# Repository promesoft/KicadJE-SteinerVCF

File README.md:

# Johansen Engineering Steiner VCF RevB

# Status - VCF working
## Initial 
| Stage  | Detail | Status |
| ------------- | ------------- | ------------- |
| create material  | sch/pcb | OK  |
| | gerber | OK |
| production  |   | OK |
|  | produced | OK |
|  | delivered | Delivered |
## Preliminary validation
| Test  | Detail | Status |
| ------------- | ------------- | ------------- |
| Initial Inspection | VCO | OK - bottom looks empty w/o gnd fill |
| Initial Inspection | VCF | OK - bottom looks empty w/o gnd fill |
| | | Very difficult to mount as footprints are getting over soldering points in many places|
| | | BP in the bottom |
| | | HP in the middle |
| | | LP on top |
| Initial Inspection | VCF SMD | OK - bottom looks empty w/o gnd fill |
| Initial Technical Test | VCO | SINE has PCB error - and Sine pot has +12V to chassis |
| Initial Technical Test | VCF | One pot gets -12v on chassis |
| Initial Technical Test | VCF SMD |  |
| Initial Product Test | VCO | Nice -  |
| Initial Product Test | VCF |  |
| | | CV1 and CV2 works fine |
| | | Q is doing something |
| | | Uncertain if the freq pot is right |
| Initial Product Test | VCF SMD|  |
## Secondary validation
| Test  | Detail | Status |
| ------------- | ------------- |------------- |
| Product Test |  | |
| Product Test |  |  |
| Quality | | |
| Quality | | |
| Long Term Product Test |  |  |
| Power Draw | VCO | +12 4mA -12
| Power Draw | VCF | +12 8mA -12
| Power Draw | VCF SMD | +12 ?mA -12

## Errata
### Errata - VCO
* Due to footprint one of the pots gets -12v on chassis

* Sine signal is shorted to GND

* Glide pot is reversed

### Errata - VCF
* Due to footprint one of the pots gets -12v on chassis

* R127 - DNP (Do not populate)

* R119 swap with 220nF-1uF to ac couple input stage

* R126 swap with 1uF to ac couple input stage

### Errata - VCF SMD

## Issues and Notes
### VCF
Very difficult to mount as footprints are getting over soldering points in many places
### VCO
 * Remove output pots
 * Collect jacks in the bottom
 * Fix errors (glide,  POT, PCB errors, footprint tightened)
 * Consider removing sine shaper
# Pictures

# Schematic

# Layout

# Inspiration

-----------------------

# Johansen Engineering Steiner VCF

# Purpose
Test some of the original designs for inspiration and reference.

# Status - Preliminary tests
## Initial 
| Stage  | Detail | Status |
| ------------- | ------------- | ------------- |
| create material  | sch/pcb | produced Rev A  |
| | gerber | produced and uploaded RevA |
| production  | ordered  | OK |
|  | produced | OK |
|  | delivered | OK |
## Preliminary validation
| Test  | Detail | Status |
| ------------- | ------------- | ------------- |
| Initial Inspection | THT VCF - Visual - Component Mounting | NOT OK |
| Initial Inspection | SMD VCF - Visual - Component Mounting | NOT OK |
| Initial Inspection | VCO  - Visual - Component Mounting | OK |
| Initial Technical Test | THT VCF - Base operation | NOT OK |
| | Knobs | Freq working for LP - Q for HP/BP - CV trim - not ok|
| Initial Technical Test | SMD VCF | NOT TESTED |
| Initial Technical Test | VCO  - Sine - Triangle - Square | OK |
| | Trimmers | OK |
| | Knobs | OK |
| Initial Product Test | VCO CV from LFO | OK |
| | VCO Vactrol CV from LFO | no real effect with CV coupling |

## Secondary validation
| Test  | Detail | Status |
| ------------- | ------------- |------------- |
| Product Test | VCF | |
| Product Test | VCO | Works nicely - frequency is a bit high |
| Quality | VCF | |
| Quality | VCO | |
| Long Term Product Test | VCO | OpAmp gets hot - esp if no output is conn to the square |
| Power Draw | VCO | 50-120mA depending on output...

## Errata
### Errata - THT VCF
 * C111 reverse polarity
 * R102 should go from +10v to connection between R103 and R106 - and +10v sould not go to Q102 base - Critical
### Errata - SMD VCF
 * R should go from +10v to connection between R and R - and +10v sould not go to Q base - Critical
### Errata - VCO
 * 470K values not correct for all resistors
 * 0R values not correct - fixed in RevB
 * Outputs should not be shorted to GND when not connected
 
## Issues and Notes
### VCF THT/SMD
 * The filter needs adjustments and the feedback is not stable. a 56k from CV to base of Q102 helps a bit.
 * Input circuit for CV needs rework
 * Input series resistor and capacitor could be a good addon for the filter inputs
 * Frequency adjust seems to work for LP only
 * Q adjust is minor and seems to work on HP and a bit on BP

### VCO
 * Tweak values for better frequency range
 * Op Amp can get hot
 * Draws more power if nothing is inserted into the Square output?

# Physical Construction

# Features

## SMD VCF Schematic

## VCO Schematic

# Inspirational sources:
## Steiner VCF 1974 THT

## Steiner VCF 1974 SMD
Same schematic - different components - half the size

## VCO ICL 8083
Based on a Thomas Henry schematic

# Details

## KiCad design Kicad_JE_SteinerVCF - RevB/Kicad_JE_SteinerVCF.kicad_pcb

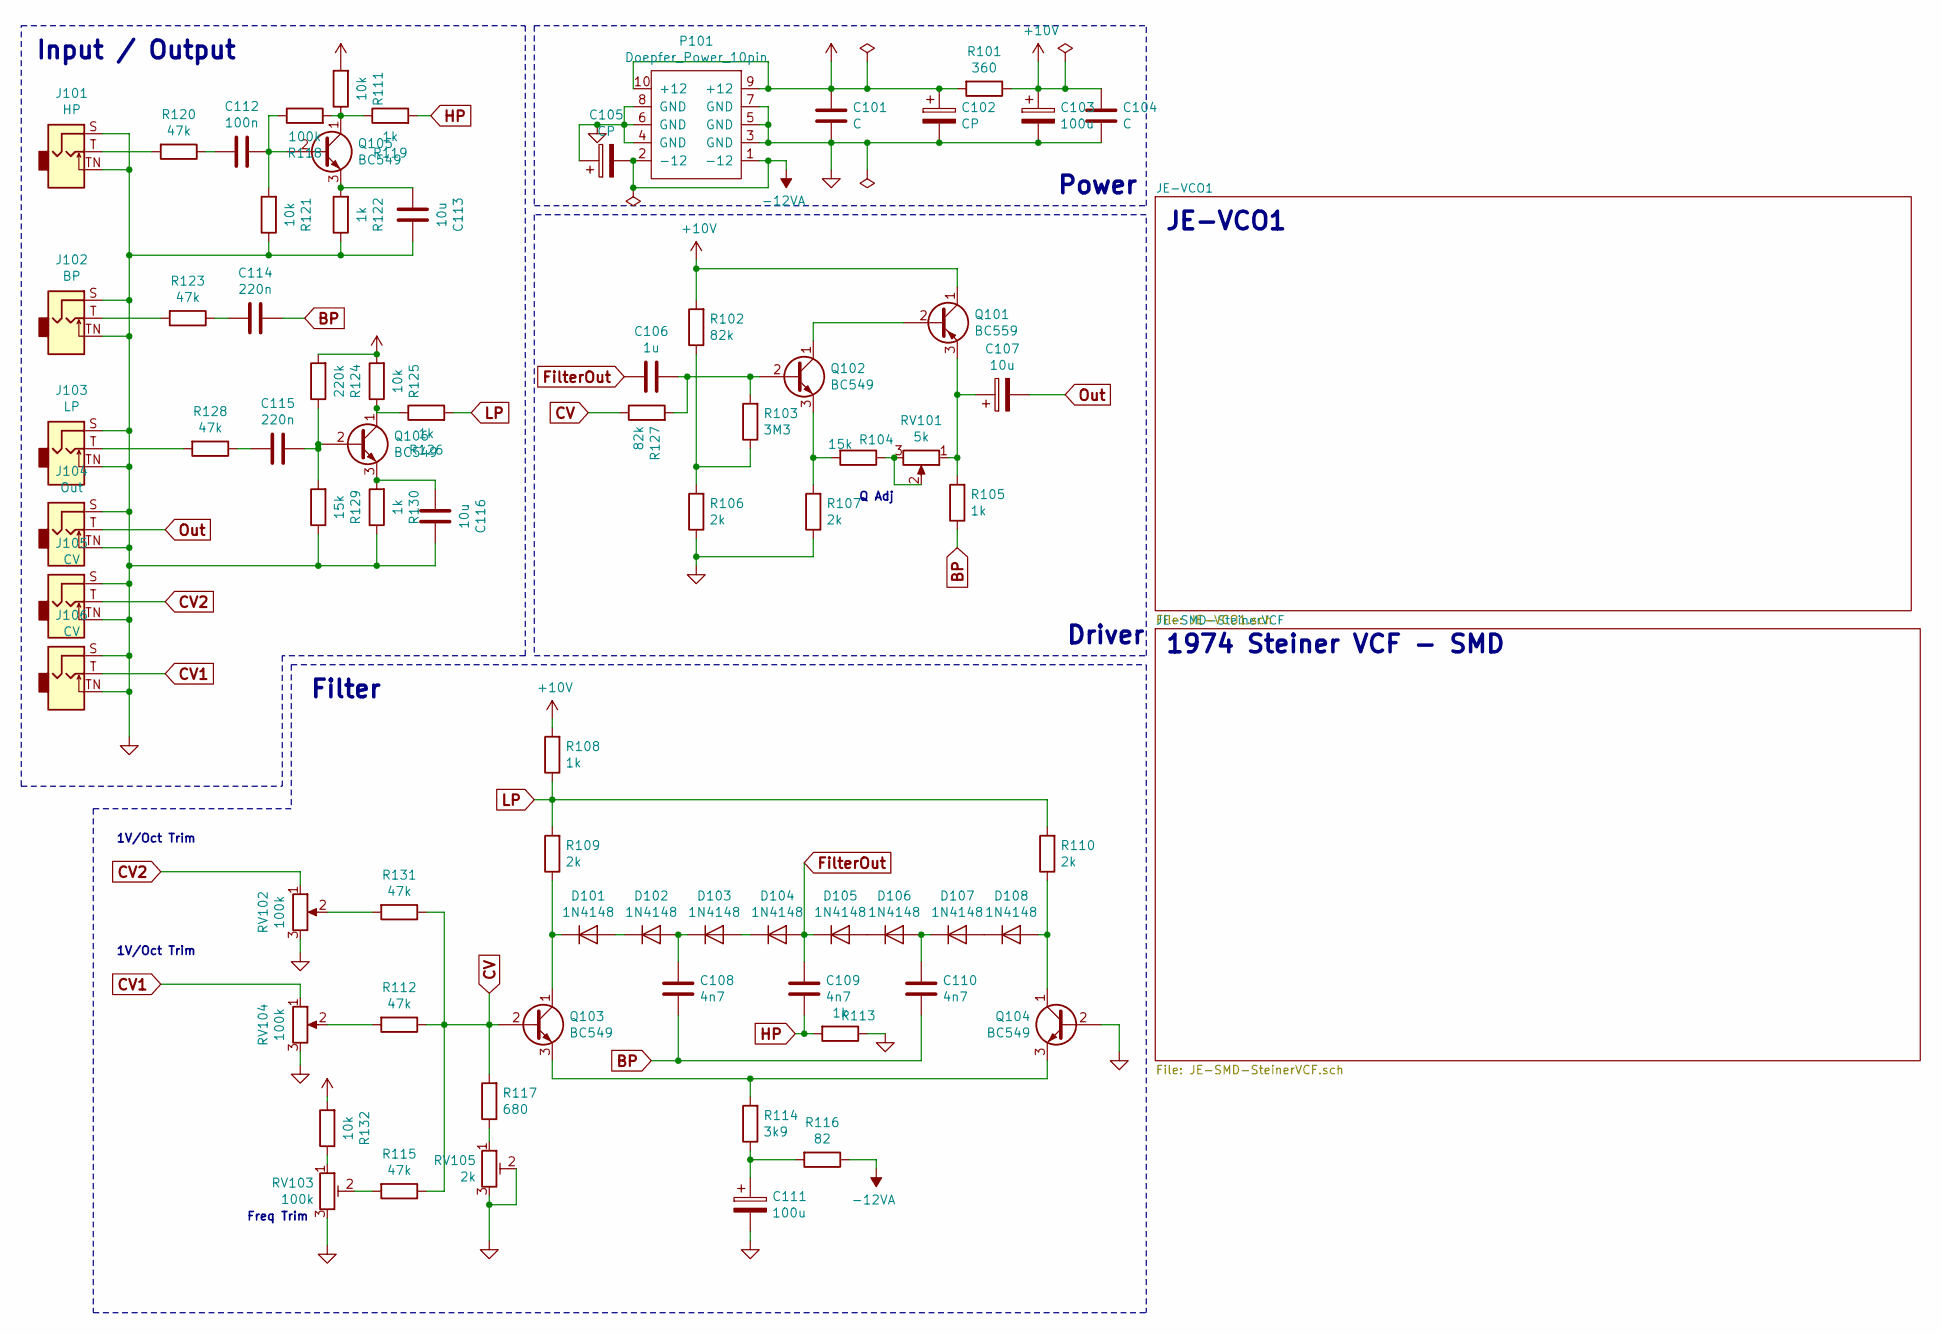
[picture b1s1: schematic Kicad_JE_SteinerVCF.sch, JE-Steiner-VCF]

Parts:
C101, C104: C; C_Rect_L7.0mm_W2.0mm_P5.00mm
C102, C105: CP; CP_Radial_D10.0mm_P5.00mm
C103, C111: 100u; CP_Radial_D10.0mm_P5.00mm
C106: 1u; C_Rect_L7.0mm_W2.0mm_P5.00mm
C107: 10u; CP_Radial_D10.0mm_P3.80mm
C108, C109, C110: 4n7; C_Rect_L7.0mm_W2.0mm_P5.00mm
C112: 100n; C_Rect_L7.0mm_W2.0mm_P5.00mm
C113, C116: 10u; C_Rect_L7.0mm_W2.0mm_P5.00mm
C114, C115: 220n; C_Rect_L7.0mm_W2.0mm_P5.00mm
D101, D102, D103, D104, D105, D106, D107, D108: 1N4148; D_DO-35_SOD27_P7.62mm_Horizontal
J101: HP; PJ301SM
J102: BP; PJ301SM
J103: LP; PJ301SM
J104: Out; PJ301SM
J105, J106: CV; PJ301SM
P101: Doepfer_Power_10pin; IDC-Header_2x05_Pitch2.54mm_Straight
Q101: BC559; TO-92_Inline
Q102, Q103, Q104, Q105, Q106: BC549; TO-92_Inline
R101: 360; R_Axial_DIN0309_L9.0mm_D3.2mm_P12.70mm_Horizontal
R102, R127: 82k; R_Axial_DIN0309_L9.0mm_D3.2mm_P12.70mm_Horizontal
R103: 3M3; R_Axial_DIN0309_L9.0mm_D3.2mm_P12.70mm_Horizontal
R104, R129: 15k; R_Axial_DIN0309_L9.0mm_D3.2mm_P12.70mm_Horizontal
R105, R108, R113, R119, R122, R126, R130: 1k; R_Axial_DIN0309_L9.0mm_D3.2mm_P12.70mm_Horizontal
R106, R107, R109, R110: 2k; R_Axial_DIN0309_L9.0mm_D3.2mm_P12.70mm_Horizontal
R111, R121, R125, R132: 10k; R_Axial_DIN0309_L9.0mm_D3.2mm_P12.70mm_Horizontal
R112, R115, R120, R123, R128, R131: 47k; R_Axial_DIN0309_L9.0mm_D3.2mm_P12.70mm_Horizontal
R114: 3k9; R_Axial_DIN0309_L9.0mm_D3.2mm_P12.70mm_Horizontal
R116: 82; R_Axial_DIN0309_L9.0mm_D3.2mm_P12.70mm_Horizontal
R117: 680; R_Axial_DIN0309_L9.0mm_D3.2mm_P12.70mm_Horizontal
R118: 100k; R_Axial_DIN0309_L9.0mm_D3.2mm_P12.70mm_Horizontal
R124: 220k; R_Axial_DIN0309_L9.0mm_D3.2mm_P12.70mm_Horizontal
RV101: 5k; Potentiometer_China_RK09_Single_Vertical_AJ
RV102, RV103, RV104: 100k; Potentiometer_China_RK09_Single_Vertical_AJ
RV105: 2k; Potentiometer_Piher_PT-6-V_Vertical

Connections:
+10V: C103.1, C104.1, Q101.1 (C), R101.1, R102.2, R108.2
+12VA: C101.1, C102.1, P101.9 (+12), P101.10 (+12), R101.2, R111.2, R124.2, R125.2, R132.2; also elsewhere on the board
-12VA: C105.2, P101.1 (-12), P101.2 (-12), R116.1; also elsewhere on the board
BP: C108.2, C110.2, C114.1, R105.1
CV: Q103.2 (B), R112.1, R115.1, R117.2, R127.1, R131.1
CV1: J106.T, RV104.1
CV2: J105.T, RV102.1
FilterOut: C106.2, C109.1, D104.2 (A), D105.1 (K)
HP: C109.2, R113.2, R119.2
LP: R108.1, R109.2, R110.2, R126.2
unnamed: C106.1, Q102.2 (B), R103.2, R127.2
unnamed: C107.1, Q101.3 (E), R105.2, RV101.1
unnamed: C108.1, D102.2 (A), D103.1 (K)
unnamed: C110.1, D106.2 (A), D107.1 (K)
unnamed: C111.1, R114.1, R116.2
unnamed: C112.1, Q105.2 (B), R118.1, R121.2
unnamed: C112.2, R120.1
unnamed: C113.2, Q105.3 (E), R122.2
unnamed: C114.2, R123.1
unnamed: C115.1, Q106.2 (B), R124.1, R129.2
unnamed: C115.2, R128.1
unnamed: C116.2, Q106.3 (E), R130.2
unnamed: D101.1 (K), Q103.1 (C), R109.1
unnamed: D101.2 (A), D102.1 (K)
unnamed: D103.2 (A), D104.1 (K)
unnamed: D105.2 (A), D106.1 (K)
unnamed: D107.2 (A), D108.1 (K)
unnamed: D108.2 (A), Q104.1 (C), R110.1
unnamed: J101.T, R120.2
unnamed: J102.T, R123.2
unnamed: J103.T, R128.2
unnamed: Q101.2 (B), Q102.1 (C)
unnamed: Q102.3 (E), R104.2, R107.2
unnamed: Q103.3 (E), Q104.3 (E), R114.2
unnamed: Q105.1 (C), R111.1, R118.2, R119.1
unnamed: Q106.1 (C), R125.1, R126.1
unnamed: R102.1, R103.1, R106.2
unnamed: R104.1, RV101.2, RV101.3
unnamed: R112.2, RV104.2
unnamed: R115.2, RV103.2
unnamed: R117.1, RV105.1
unnamed: R131.2, RV102.2
unnamed: R132.1, RV103.1
Out: C107.2, J104.T

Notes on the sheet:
Power
Freq Trim
1V/Oct Trim
Filter
Driver
Q Adj
1974 Steiner VCF - SMD
JE-VCO1
Input / Output

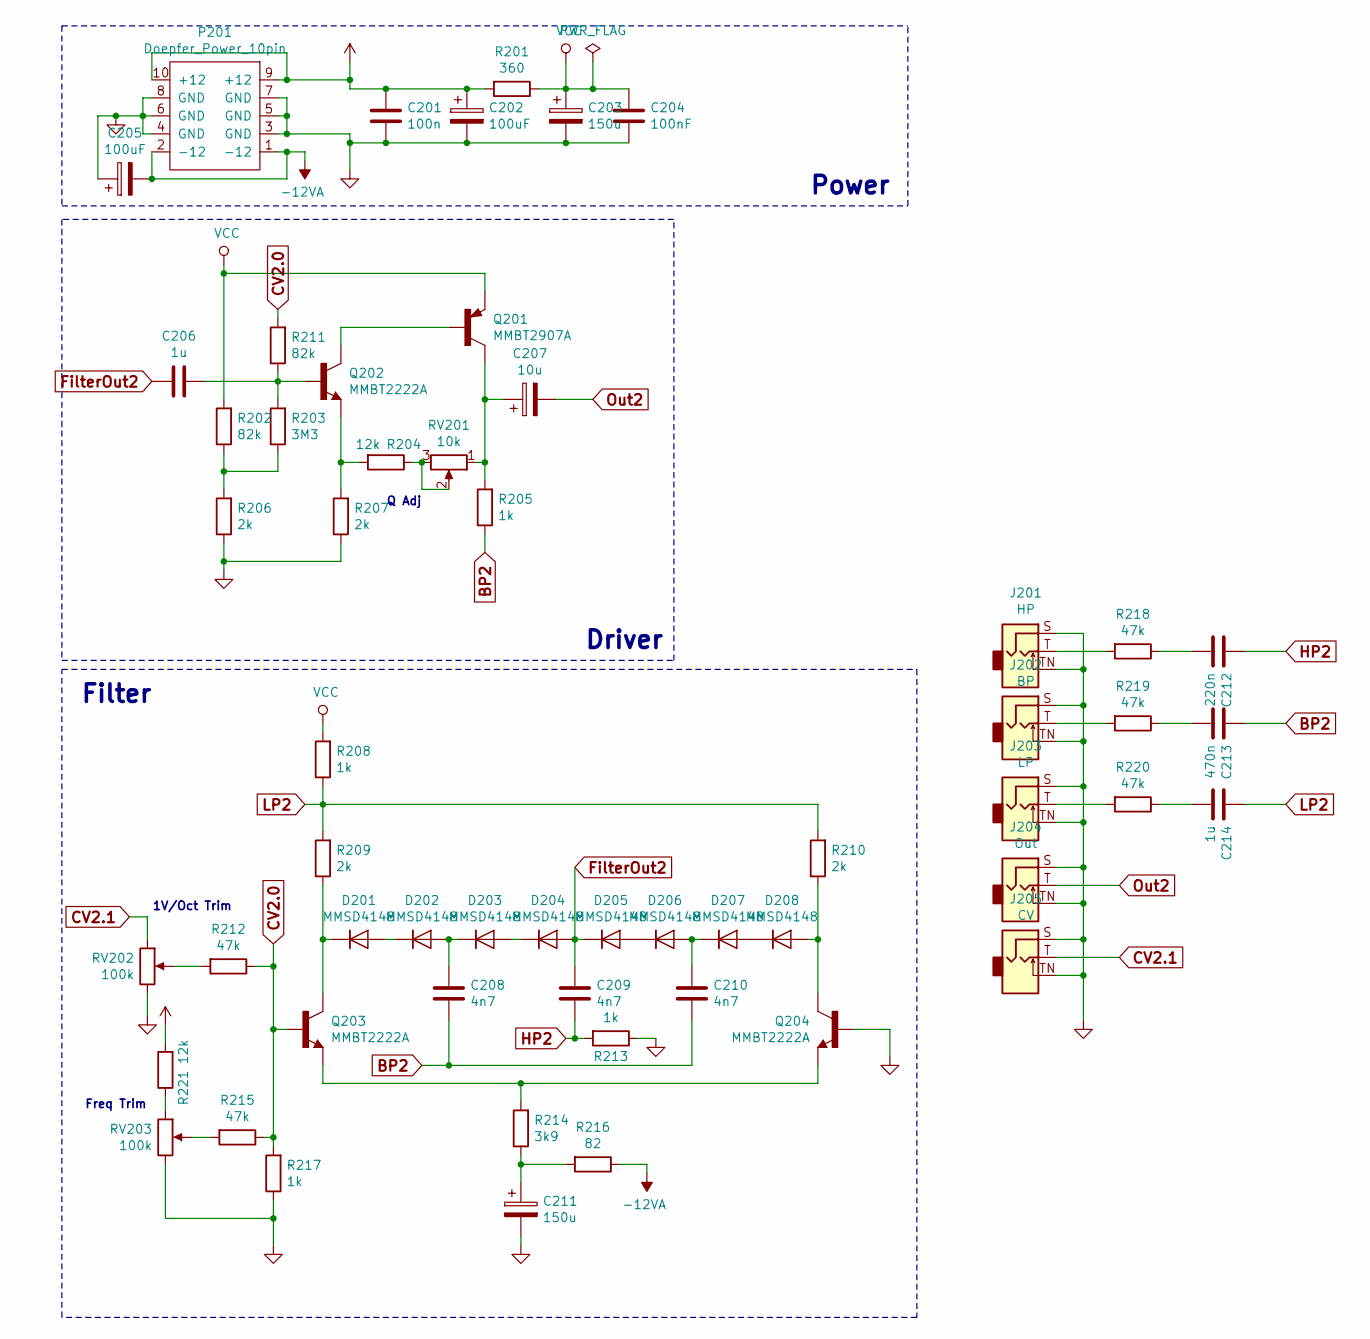
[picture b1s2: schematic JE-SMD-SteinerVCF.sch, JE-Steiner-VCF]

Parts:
C201: 100n; C_0805_2012Metric_Pad1.15x1.40mm_HandSolder
C202, C205: 100uF; CP_EIA-7343-15_Kemet-W_Pad2.25x2.55mm_HandSolder
C203, C211: 150u; CP_Radial_D10.0mm_P5.00mm
C204: 100nF; C_0805_2012Metric_Pad1.15x1.40mm_HandSolder
C206, C214: 1u; C_0805_2012Metric_Pad1.15x1.40mm_HandSolder
C207: 10u; C_0805_2012Metric_Pad1.15x1.40mm_HandSolder
C208, C209, C210: 4n7; C_0805_2012Metric_Pad1.15x1.40mm_HandSolder
C212: 220n; C_0805_2012Metric_Pad1.15x1.40mm_HandSolder
C213: 470n; C_0805_2012Metric_Pad1.15x1.40mm_HandSolder
D201, D202, D203, D204, D205, D206, D207, D208: MMSD4148; D_SOD-123
J201: HP; PJ301SM
J202: BP; PJ301SM
J203: LP; PJ301SM
J204: Out; PJ301SM
J205: CV; PJ301SM
P201: Doepfer_Power_10pin; IDC-Header_2x05_Pitch2.54mm_Straight
Q201: MMBT2907A; SOT-23-3
Q202, Q203, Q204: MMBT2222A; SOT-23-3
R201: 360; R_0805_2012Metric_Pad1.15x1.40mm_HandSolder
R202, R211: 82k; R_0805_2012Metric_Pad1.15x1.40mm_HandSolder
R203: 3M3; R_0805_2012Metric_Pad1.15x1.40mm_HandSolder
R204, R221: 12k; R_0805_2012Metric_Pad1.15x1.40mm_HandSolder
R205, R208, R213, R217: 1k; R_0805_2012Metric_Pad1.15x1.40mm_HandSolder
R206, R207, R209, R210: 2k; R_0805_2012Metric_Pad1.15x1.40mm_HandSolder
R212, R215, R218, R219, R220: 47k; R_0805_2012Metric_Pad1.15x1.40mm_HandSolder
R214: 3k9; R_0805_2012Metric_Pad1.15x1.40mm_HandSolder
R216: 82; R_0805_2012Metric_Pad1.15x1.40mm_HandSolder
RV201: 10k; Potentiometer_Alps_RK09K_Single_Vertical
RV202, RV203: 100k; AlpsRK09K

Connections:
+12VA: C201.1, C202.1, P201.9 (+12), P201.10 (+12), R201.2, R221.2; also elsewhere on the board
-12VA: C205.2, P201.1 (-12), P201.2 (-12), R216.1; also elsewhere on the board
BP2: C208.2, C210.2, C213.1, R205.1
CV2.0: Q203.1 (B), R211.2, R212.1, R215.1, R217.2
CV2.1: J205.T, RV202.1
FilterOut2: C206.2, C209.1, D204.2 (A), D205.1 (K)
HP2: C209.2, C212.1, R213.2
LP2: C214.1, R208.1, R209.2, R210.2
unnamed: C206.1, Q202.1 (B), R203.2, R211.1
unnamed: C207.1, Q201.3 (C), R205.2, RV201.1
unnamed: C208.1, D202.2 (A), D203.1 (K)
unnamed: C210.1, D206.2 (A), D207.1 (K)
unnamed: C212.2, R218.1
unnamed: C213.2, R219.1
unnamed: C214.2, R220.1
unnamed: D201.1 (K), Q203.3 (C), R209.1
unnamed: D201.2 (A), D202.1 (K)
unnamed: D203.2 (A), D204.1 (K)
unnamed: D205.2 (A), D206.1 (K)
unnamed: D207.2 (A), D208.1 (K)
unnamed: D208.2 (A), Q204.3 (C), R210.1
unnamed: J201.T, R218.2
unnamed: J202.T, R219.2
unnamed: J203.T, R220.2
unnamed: Q201.1 (B), Q202.3 (C)
unnamed: Q202.2 (E), R204.2, R207.2
unnamed: Q203.2 (E), Q204.2 (E), R214.2
unnamed: R202.1, R203.1, R206.2
unnamed: R204.1, RV201.2, RV201.3
unnamed: R212.2, RV202.2
unnamed: R215.2, RV203.2
unnamed: R221.1, RV203.1
Out2: C207.2, J204.T
VCC: C203.1, C204.1, Q201.2 (E), R201.1, R202.2, R208.2

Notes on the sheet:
Power
Freq Trim
1V/Oct Trim
Filter
Driver
Q Adj

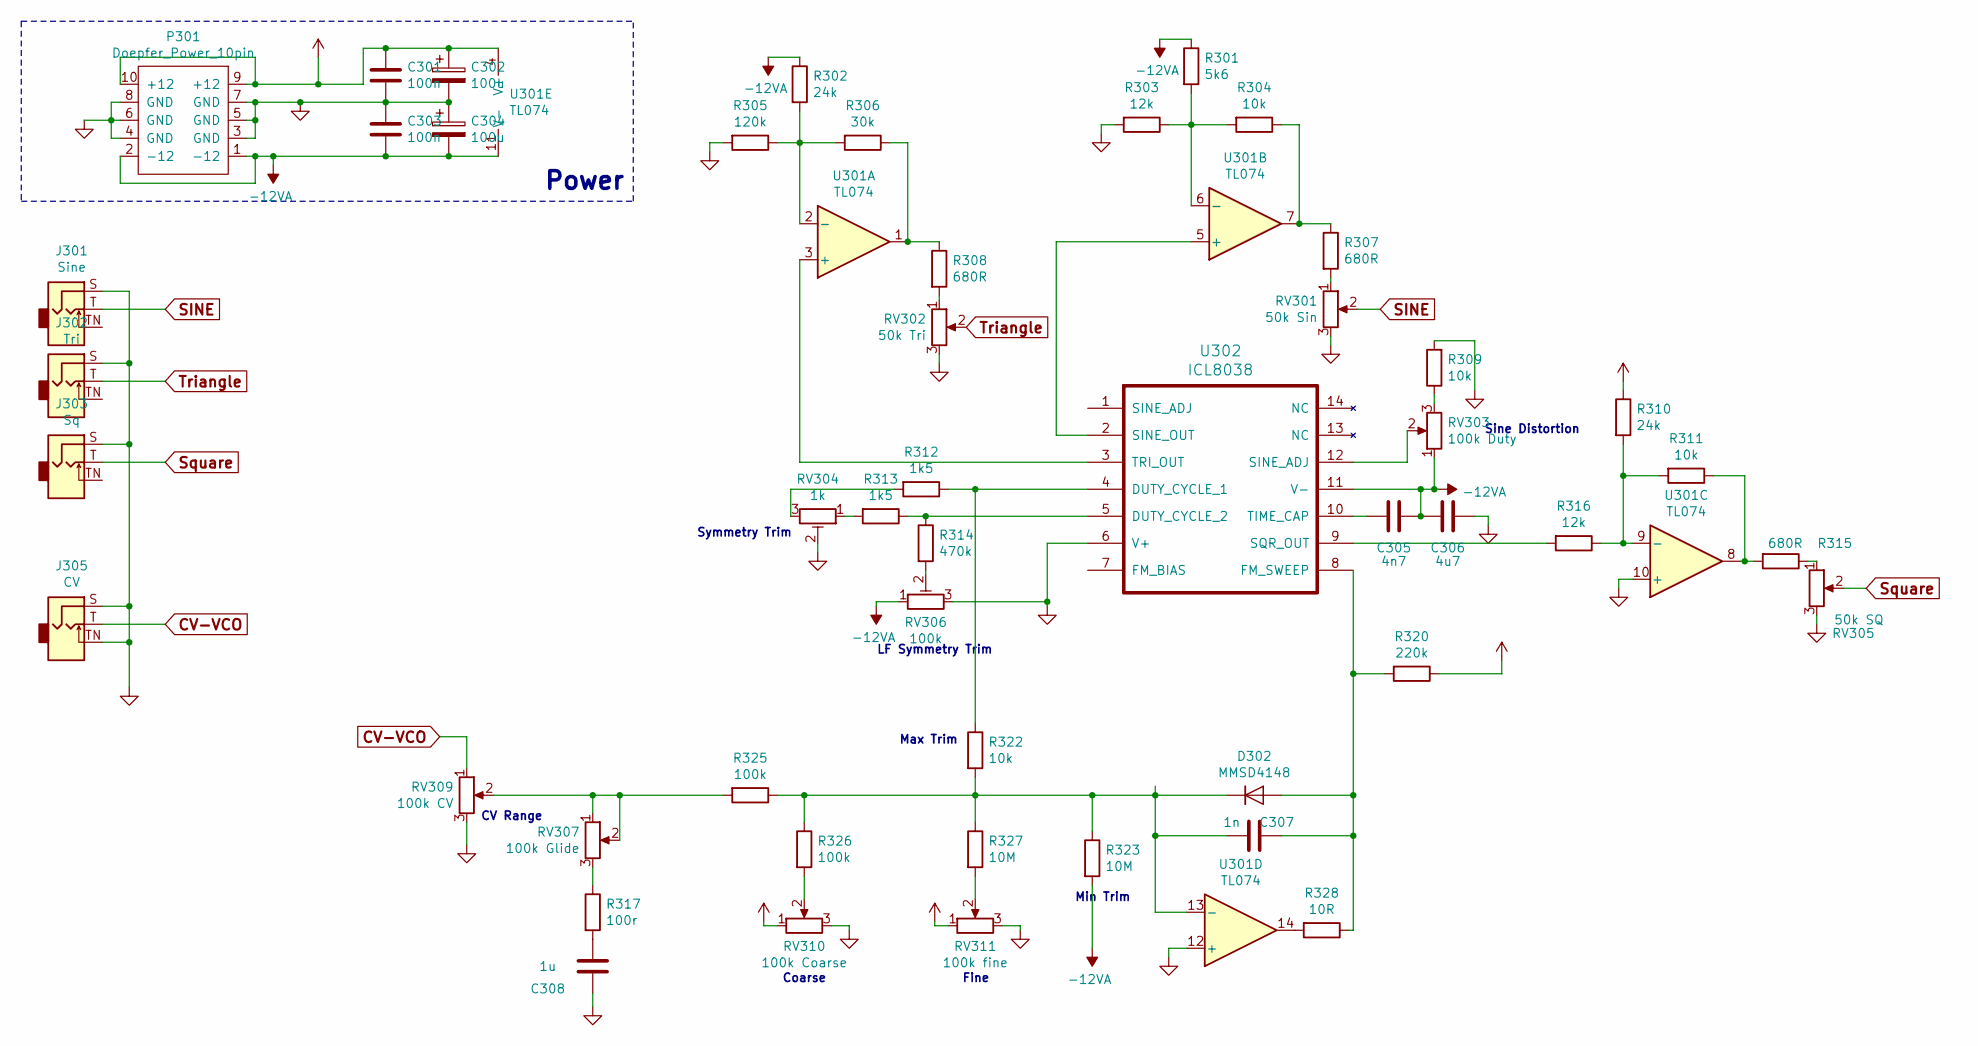
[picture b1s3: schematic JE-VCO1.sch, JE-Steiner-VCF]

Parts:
C301, C303: 100n; C_0805_2012Metric_Pad1.15x1.40mm_HandSolder
C302, C304: 100u; C_1206_3216Metric
C305: 4n7; C_0805_2012Metric_Pad1.15x1.40mm_HandSolder
C306: 4u7; C_0805_2012Metric_Pad1.15x1.40mm_HandSolder
C307: 1n; C_0805_2012Metric_Pad1.15x1.40mm_HandSolder
C308: 1u; C_0805_2012Metric_Pad1.15x1.40mm_HandSolder
D302: MMSD4148; D_MiniMELF
J301: Sine; PJ301SM
J302: Tri; PJ301SM
J303: Sq; PJ301SM
J305: CV; PJ301SM
P301: Doepfer_Power_10pin; IDC-Header_2x05_Pitch2.54mm_Straight
R301: 5k6; R_0805_2012Metric_Pad1.15x1.40mm_HandSolder
R302, R310: 24k; R_0805_2012Metric_Pad1.15x1.40mm_HandSolder
R303, R316: 12k; R_0805_2012Metric_Pad1.15x1.40mm_HandSolder
R304, R309, R311, R322: 10k; R_0805_2012Metric_Pad1.15x1.40mm_HandSolder
R305: 120k; R_0805_2012Metric_Pad1.15x1.40mm_HandSolder
R306: 30k; R_0805_2012Metric_Pad1.15x1.40mm_HandSolder
R307, R308, R315: 680R; R_0805_2012Metric_Pad1.15x1.40mm_HandSolder
R312, R313: 1k5; R_0805_2012Metric_Pad1.15x1.40mm_HandSolder
R314: 470k; R_0805_2012Metric_Pad1.15x1.40mm_HandSolder
R317: 100r; R_0805_2012Metric_Pad1.15x1.40mm_HandSolder
R320: 220k; R_0805_2012Metric_Pad1.15x1.40mm_HandSolder
R323, R327: 10M; R_0805_2012Metric_Pad1.15x1.40mm_HandSolder
R325, R326: 100k; R_0805_2012Metric_Pad1.15x1.40mm_HandSolder
R328: 10R; R_0805_2012Metric_Pad1.15x1.40mm_HandSolder
RV301: 50k Sin; Potentiometer_China_RK09_Single_Vertical_AJ
RV302: 50k Tri; Potentiometer_China_RK09_Single_Vertical_AJ
RV303: 100k Duty; Potentiometer_China_RK09_Single_Vertical_AJ
RV304: 1k; Potentiometer_Piher_PT-6-V_Vertical
RV305: 50k SQ; Potentiometer_China_RK09_Single_Vertical_AJ
RV306: 100k; Potentiometer_Piher_PT-6-V_Vertical
RV307: 100k Glide; Potentiometer_China_RK09_Single_Vertical_AJ
RV309: 100k CV; Potentiometer_China_RK09_Single_Vertical_AJ
RV310: 100k Coarse; Potentiometer_China_RK09_Single_Vertical_AJ
RV311: 100k fine; Potentiometer_China_RK09_Single_Vertical_AJ
U301: TL074; SOIC-14_3.9x8.7mm_P1.27mm
U302: ICL8038; DIP-14_W7.62mm

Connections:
+12VA: C301.1, C302.1, P301.9 (+12), P301.10 (+12), R310.1, R320.1, RV310.1, RV311.1, U301.4 (V+); also elsewhere on the board
-12VA: C303.2, C304.2, C305.1, C306.2, P301.1 (-12), P301.2 (-12), R301.1, R302.1, R323.2, RV303.1, RV306.1, U301.11 (V-), U302.11 (V-); also elsewhere on the board
CV-VCO: J305.T, RV309.1
unnamed: C305.2, U302.10 (TIME_CAP)
unnamed: C307.1, D302.2 (A), R320.2, R328.1, U302.8 (FM_SWEEP)
unnamed: C307.2, D302.1 (K), R322.2, R323.1, R325.1, R326.1, R327.1, U301.13 (-)
unnamed: C308.2, R317.2
unnamed: R301.2, R303.1, R304.2, U301.6 (-)
unnamed: R302.2, R305.1, R306.2, U301.2 (-)
unnamed: R304.1, R307.1, U301.7
unnamed: R306.1, R308.1, U301.1
unnamed: R307.2, RV301.1
unnamed: R308.2, RV302.1
unnamed: R309.1, RV303.3
unnamed: R310.2, R311.2, R316.1, U301.9 (-)
unnamed: R311.1, R315.2, U301.8
unnamed: R312.1, R322.1, U302.4 (DUTY_CYCLE_1)
unnamed: R312.2, RV304.3
unnamed: R313.1, R314.1, U302.5 (DUTY_CYCLE_2)
unnamed: R313.2, RV304.1
unnamed: R314.2, RV306.2
unnamed: R315.1, RV305.1
unnamed: R316.2, U302.9 (SQR_OUT)
unnamed: R317.1, RV307.3
unnamed: R325.2, RV307.1, RV307.2, RV309.2
unnamed: R326.2, RV310.2
unnamed: R327.2, RV311.2
unnamed: R328.2, U301.14
unnamed: RV303.2, U302.12 (SINE_ADJ)
unnamed: U301.3 (+), U302.3 (TRI_OUT)
unnamed: U301.5 (+), U302.2 (SINE_OUT)
SINE: J301.T, RV301.2
Square: J303.T, RV305.2
Triangle: J302.T, RV302.2

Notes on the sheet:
Power
Sine Distortion
Symmetry Trim
LF Symmetry Trim
CV Range
Coarse
Fine
Max Trim
Min Trim

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
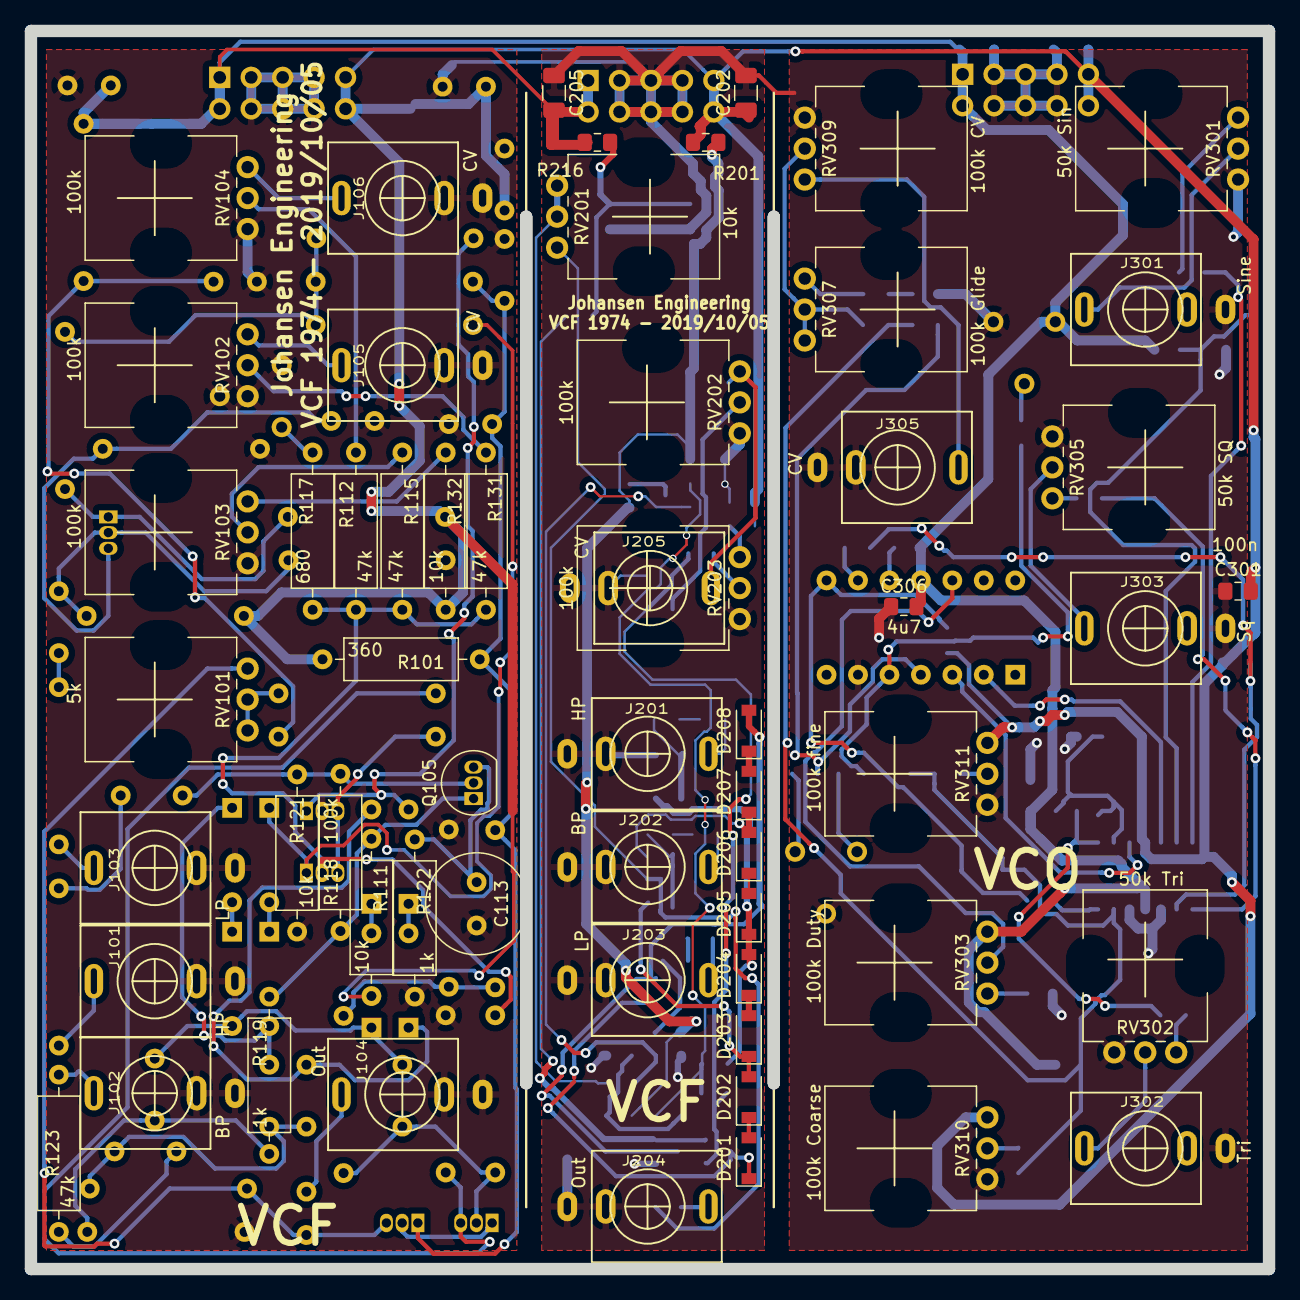
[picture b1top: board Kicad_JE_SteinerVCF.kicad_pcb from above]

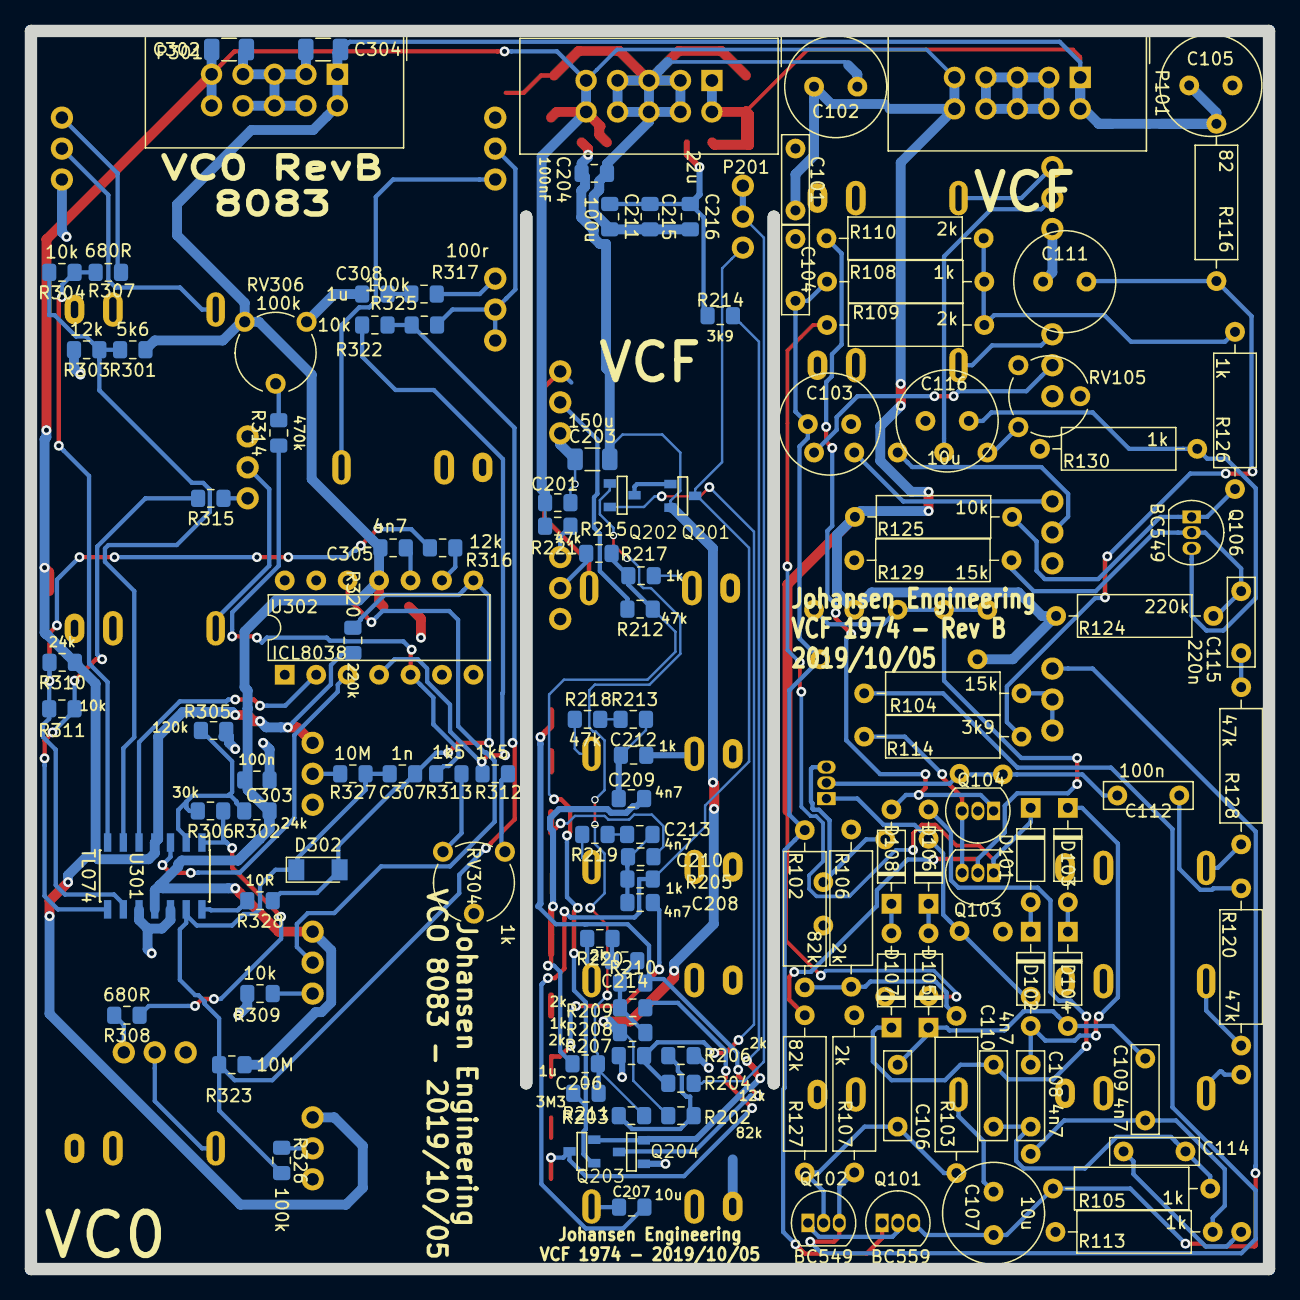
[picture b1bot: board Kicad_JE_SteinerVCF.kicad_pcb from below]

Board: 2 copper layers, 100.0 x 100.0 mm, 182 parts (124 on the bottom side), 110 nets.

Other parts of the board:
C215, C216: 22u; C_0805_2012Metric_Pad1.15x1.40mm_HandSolder

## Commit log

2019-01-18 Original article
    from http://yusynth.net/Modular/index_en.html
2019-01-19 Initial schematic - missing driver section
2019-01-19 Initial complete RevA sch
2019-01-19 SMD sub sheet
2019-01-20 ERC, Footprints and Annotation in SCH
2019-01-20 Net - names conn
2019-01-20 Place SMD init
2019-01-20 SMD section routed RevA
2019-01-20 THT Start - Label upd
2019-01-20 THT update - minor
2019-01-20 THT complete placement - RevA
2019-01-20 Connection Cleanup on both VCF
2019-01-20 Label Placement SMD and THT - RevA
2019-01-20 pict
2019-01-20 ICL8083 VCO added sch, ERC and footprints
2019-01-20 VCO ICL8083 netlist and PCB import
2019-01-20 Components for faceplate mounted
2019-01-21 VCO inspiration
2019-01-24 PNG Sch update VCO
2019-01-26 PCB - Components placed on VCO
2019-01-26 All routed - And 3D
2019-01-26 Text
2019-01-26 Gerber and DRC
2019-01-26 New Gerber
2019-01-26 BOM generated
2019-02-02 Images
2019-02-19 RevB init
2019-02-19 VCF Rev B THT + Extra inspiration
2019-02-19 fix reintroduced
2019-02-19 mod fix
2019-02-19 RevB SMD
2019-02-19 VCF SMD
2019-02-19 VCO minor
2019-02-20 VCO 0R indicate
2019-02-20 vco updated values
2019-02-20 prototype pictures
2019-02-21 Fiddling around with image orientation and github updates
2019-02-21 Minor
2019-03-16 RevB Sch initiated
2019-03-16 RevB second step
2019-03-16 DRC RevB
2019-03-16 Label sheets
2019-03-16 JPG incl faceplate
2019-03-16 SteinerVCF_SMD.png
2019-03-16 VCO_ICL8083 Schematic.png
2019-10-05 Rev B init
2019-10-05 8083 routed
2019-10-05 VCF SMD routed
2019-10-05 fiddleing w THT VCF
2019-10-05 VCF THT Placed
2019-10-05 Routed THT
2019-10-05 Labels
2019-10-05 Gerber
2020-03-31 SMD sch pict
2020-04-11 naming
